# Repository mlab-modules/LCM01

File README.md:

# LCM01 - L and C meter

Inductor and capacitor measuring analog front end.

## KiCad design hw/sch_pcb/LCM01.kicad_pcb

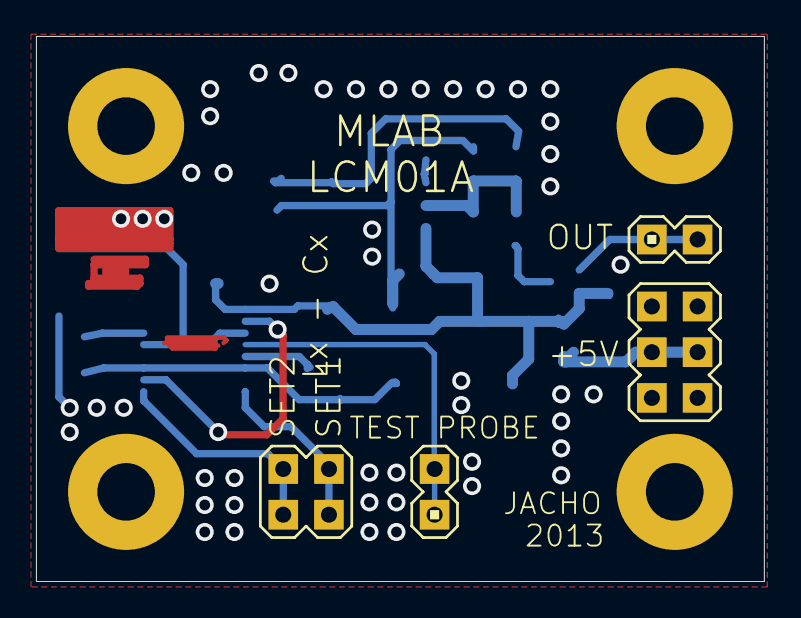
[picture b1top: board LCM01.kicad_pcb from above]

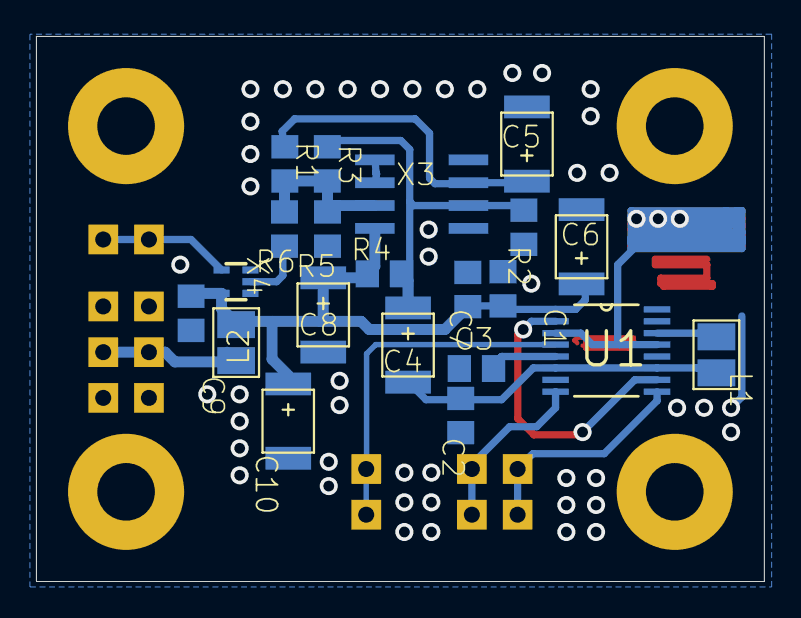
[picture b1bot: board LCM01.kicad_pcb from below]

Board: 2 copper layers, 40.4 x 30.3 mm, 30 parts (21 on the bottom side), 17 nets.

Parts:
C1, C7, C9: 100nF; C0805
C2: 680pF; C0805
C3: 1nF presny; C0805
C4, C5, C6, C10: 10u/10V; B
C8: 10uF/10V; B
CX-LX0: SPEC_805
L1: 68uH presny; 1210
L2: BLM21PG300SN1D; 1210
R1: 47k; 0805
R2, R3, R4: 100k; 0805
R5: 1k; 0805
R6: 0; 0805
SV1: MA02-2
SV2: MA03-2
SV3, SV4: MA02-1
U1: ADG888YRUZ; SOP65P640X120-16N
X1, X2, X6, X7: SROUB3M
X3: LM311; SO8
X4: 74HC1G14; SOT353

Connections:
C+: CX-LX0.2, U1.3, U1.13
GND: C1.2, C2.1, C3.1, C5.-, C6.-, C7.2, C8.-, C9.2, C10.-, CX-LX0.1, R2.1, SV2.1, SV2.2, SV2.5, SV2.6, U1.15, U1.16, X1.P$1, X2.P$1, X3.1, X3.4, X4.3, X6.P$1, X7.P$1
unnamed: C2.2, C4.-, L1.P$1, U1.6, U1.11
unnamed: X3.5, X3.6
unnamed: C3.2, U1.5
unnamed: U1.2, U1.10
unnamed: SV1.1, SV1.2, U1.8
unnamed: SV3.1, SV3.2, U1.4
unnamed: L1.P$2, U1.14
unnamed: C5.+, R1.2, X3.3
unnamed: R1.1, R3.1, R5.1, R6.2, X3.7
unnamed: SV1.3, SV1.4, U1.9
unnamed: R6.1, X4.2
unnamed: C4.+, R2.2, R3.2, R4.1, X3.2
unnamed: SV4.1, SV4.2, X4.4
NAP: C1.1, C6.+, C7.1, C8.+, C9.1, C10.+, L2.P$1, R4.2, U1.1, X3.8, X4.5
VCC: L2.P$2, SV2.3, SV2.4

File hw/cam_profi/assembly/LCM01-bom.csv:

Component,Description,Part,References,Value,Footprint,Quantity Per PCB,Datasheet
1,,C0805,C2,680pF,C0805,1,
2,,C0805,C1C7C9,100nF,C0805,3,
3,,B,C4C5C6C10,10u/10V,B,4,
4,,B,C8,10uF/10V,B,1,
5,,C0805,C3,1nF presny,C0805,1,
6,,SPEC_805,CX-LX0,SPEC_805,SPEC_805,1,
7,,L1210,L1,68uH presny,1210,1,
8,,L1210,L2,BLM21PG300SN1D,1210,1,
9,,R0805,R6,0,0805,1,
10,,R0805,R5,1k,0805,1,
11,,R0805,R1,47k,0805,1,
12,,R0805,R2R3R4,100k,0805,3,
13,,MA02-1,SV3SV4,MA02-1,MA02-1,2,
14,,MA02-2,SV1,MA02-2,MA02-2,1,
15,,MA03-2,SV2,MA03-2,MA03-2,1,
16,,ADG888YRUZ,U1,ADG888YRUZ,SOP65P640X120-16N,1,
17,,74HC1G14,X4,74HC1G14,SOT353,1,
18,,LM311,X3,LM311,SO8,1,
19,,SROUB3M,X1X2X6X7,SROUB3M,SROUB3M,4,

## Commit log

2023-04-01 Adding force option to enable splitting in not fresh copy of Modules repository.
2023-05-28 automated commit; add github actions
2023-05-28 Update workflow files
2023-05-28 Update metadata files
2023-07-05 automated commit; rename source files to new naming convence
2023-09-16 Update status
2024-07-04 Convert Eagle project to KiCAdv7.
2024-07-04 Update actions products
2024-07-04 Update readme.
